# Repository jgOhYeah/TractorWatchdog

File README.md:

# TractorWatchdog
Engine watchdog for a Fordson Dexta tractor. Should work with other tractors as well.

Doxygen documentation is available [here](https://jgohyeah.github.io/TractorWatchdog/).

## Block diagram

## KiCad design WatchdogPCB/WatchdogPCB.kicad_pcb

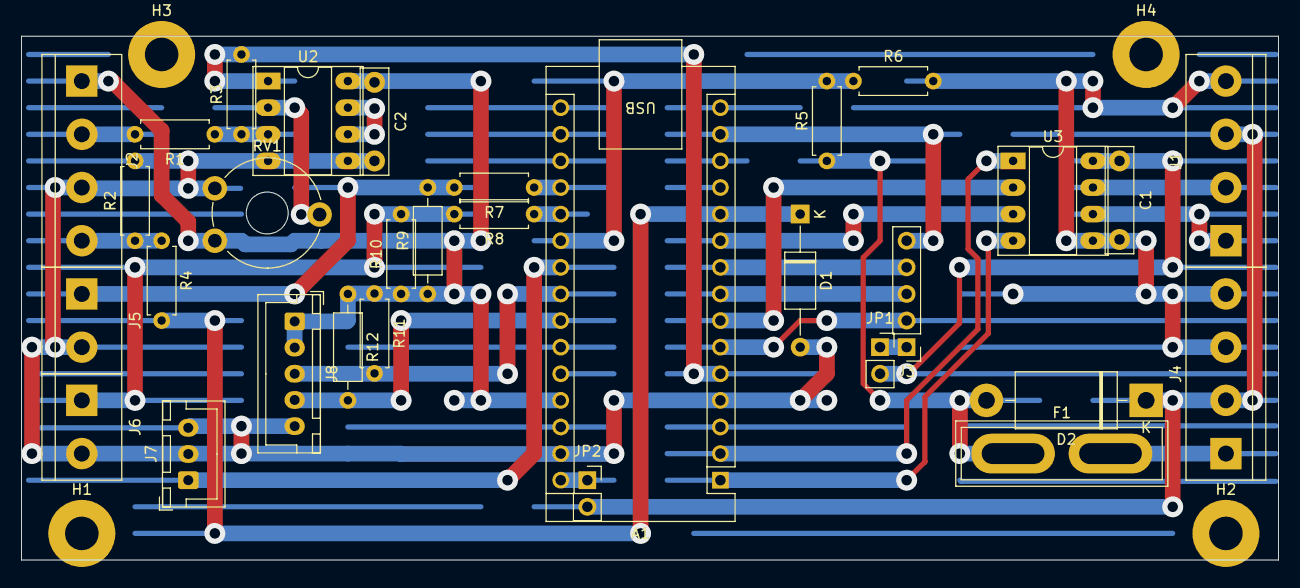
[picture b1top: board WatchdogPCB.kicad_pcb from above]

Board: 4 copper layers, 120.0 x 50.0 mm, 35 parts (0 on the bottom side), 32 nets.

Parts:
A1: Arduino_Nano_v3.x; Arduino_Nano
C1, C2: 10n; C_Rect_L10.0mm_W2.5mm_P7.50mm_MKS4
D1: 5.1V; D_A-405_P12.70mm_Horizontal
D2: 1N5404; D_DO-201AD_P15.24mm_Horizontal
F1: 3A; Fuse_Blade_ATO_directSolder
H1, H2, H3, H4: MountingHole; MountingHole_3.2mm_M3_Pad
J1: Roll hoop; TerminalBlock_bornier-4_P5.08mm
J2: Speed & Oil; TerminalBlock_bornier-4_P5.08mm
J3: H bridge driver control; PinHeader_1x05_P2.54mm_Vertical
J4: Power; TerminalBlock_bornier-4_P5.08mm
J5: Thermistor 1; TerminalBlock_bornier-2_P5.08mm
J6: Thermistor 2; TerminalBlock_bornier-2_P5.08mm
J7: Dashboard A; JST_XH_B3B-XH-A_1x03_P2.50mm_Vertical
J8: Dashboard B; JST_XH_B5B-XH-A_1x05_P2.50mm_Vertical
JP1: 5V jumper; PinSocket_1x02_P2.54mm_Vertical
JP2: 12V jumper; PinSocket_1x02_P2.54mm_Vertical
R1, R4, R11: 4.7k; R_Axial_DIN0207_L6.3mm_D2.5mm_P7.62mm_Horizontal
R2, R7, R8: 1k; R_Axial_DIN0207_L6.3mm_D2.5mm_P7.62mm_Horizontal
R3: 120k; R_Axial_DIN0207_L6.3mm_D2.5mm_P7.62mm_Horizontal
R5: 100k; R_Axial_DIN0207_L6.3mm_D2.5mm_P7.62mm_Horizontal
R6: 39k; R_Axial_DIN0207_L6.3mm_D2.5mm_P7.62mm_Horizontal
R9: 470; R_Axial_DIN0207_L6.3mm_D2.5mm_P10.16mm_Horizontal
R10: 470; R_Axial_DIN0207_L6.3mm_D2.5mm_P7.62mm_Horizontal
R12: 4.7k; R_Axial_DIN0207_L6.3mm_D2.5mm_P10.16mm_Horizontal
RV1: 10k; Potentiometer_Piher_PT-10-V10_Vertical_Hole
U2: MCP602; DIP-8_W7.62mm_Socket_LongPads
U3: DS3695N; DIP-8_W7.62mm_Socket_LongPads

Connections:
+5V: A1.27 (+5V), C1.1, C2.1, J2.1, J8.1, J8.2, JP1.2 (B), R9.1, R10.1, R11.1, R12.1, RV1.1, U2.8 (V+), U3.8 (VCC)
+12V: D2.1 (K), J1.3, J4.2, JP2.2 (B)
+BATT: D2.2 (A), F1.1, R5.1
+VDC: F1.2, J4.1
/Main PCB/+RS485: J1.1, U3.6 (DO/RI)
/Main PCB/-RS485: J1.2, U3.7 (~DO/RI)
/Main PCB/Aux: A1.14 (D11), J3.5
/Main PCB/Dash. BTN: A1.22 (A3), J7.1
/Main PCB/Dash. SCL: A1.24 (A5), J8.4, R12.2
/Main PCB/Dash. SDA: A1.23 (A4), J8.3, R11.2
/Main PCB/Horn: A1.9 (D6), J3.4
/Main PCB/Motor A: A1.6 (D3), J3.2
/Main PCB/Motor B: A1.8 (D5), J3.3
/Main PCB/Motor driver 5V: J3.1, JP1.1 (A)
/Main PCB/Oil SW: J2.4, R2.1, R4.1
/Main PCB/Tach. hall: J2.2, R1.2
/Main PCB/Thermistor 1: J5.1, R7.2, R9.2
/Main PCB/Thermistor 2: J6.1, R8.2, R10.2
/Main PCB/Threshold adjust: RV1.2, U2.2 (-)
GND: A1.4 (GND), A1.29 (GND), C1.2, C2.2, D1.2 (A), J1.4, J2.3, J4.3, J4.4, J5.2, J6.2, J7.2, J7.3, J8.5, R2.2, R6.2, RV1.3, U2.4 (V-), U2.5 (+), U3.5 (GND)
unnamed: A1.19 (A0), R7.1
unnamed: A1.20 (A1), R8.1
unnamed: A1.21 (A2), R5.2, R6.1
unnamed: A1.2 (D0/RX), U3.1 (RO)
unnamed: A1.1 (D1/TX), U3.4 (DI)
unnamed: A1.5 (D2), R3.2, U2.1
unnamed: A1.7 (D4), U3.2 (~RE)
unnamed: A1.10 (D7), U3.3 (DE)
unnamed: A1.11 (D8), D1.1 (K), R4.2
unnamed: A1.30 (VIN), JP2.1 (A)
unnamed: R1.1, R3.1, U2.3 (+)
unnamed: U2.6 (-), U2.7

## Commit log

2023-10-03 Started Arduno code
2023-10-03 Started PCB schematic
2023-10-03 About display works, display structure ongoing
2023-10-03 Home and error displays started, display managing works
2023-10-03 Home and error displays show data
2023-10-03 Temperature and voltage displays should work.
2023-10-03 drawState automatically called for the active state only
2023-10-03 Added doxygen
2023-10-03 Added readme file to doxygen with block diagram
2023-10-03 Deploying to gh-pages from @ jgOhYeah/TractorWatchdog@66a84c4cfc01eea5ef9e85b0e8ce081e668e4cee 🚀
2023-10-03 Initial gh-pages commit
2023-10-11 Started working on dashboard enclosure
2023-10-11 Deploying to gh-pages from @ jgOhYeah/TractorWatchdog@f4bf1ece06eab8d8c2045e530ada4d6bf3068222 🚀
2023-10-11 Chunky dashboard enclosure design completed
2023-10-12 Mechanical side of main unit designed
2023-10-12 Working on electronics enclosure
2023-10-13 Working on the schematic
2023-10-13 Schematic finished
2023-10-13 Layout mostly done
2023-10-14 Made fold go in two parts
2023-10-14 Board layout as contructed
2023-10-15 Added button to UI
2023-10-15 Deploying to gh-pages from @ jgOhYeah/TractorWatchdog@bb199354caf6e690c3105aca5bad56b1517cbab6 🚀
2023-10-15 Autoformatting
2023-10-15 Most sensors added
2023-10-15 Deploying to gh-pages from @ jgOhYeah/TractorWatchdog@bedf9a79883e9635bca10e1fcfefe7930e42f3a0 🚀
2023-10-15 Added state checking, motor control, init screens and bug fixes
2023-10-15 Deploying to gh-pages from @ jgOhYeah/TractorWatchdog@d0365db719fc78dc5e4a14963c554e48b9c63fa7 🚀
2023-10-16 Added timekeeping capabilities hopefully
2023-10-16 Deploying to gh-pages from @ jgOhYeah/TractorWatchdog@f8c32a56cf8dc41646a823f7055e96f66b06238e 🚀
2023-10-17 Demonstration ready
2023-10-17 Deploying to gh-pages from @ jgOhYeah/TractorWatchdog@8c00ade64e00c7b973194b41744bc4b3d9e471bb 🚀
2023-11-02 Tidying up, added credits display back again
2023-11-02 Deploying to gh-pages from @ jgOhYeah/TractorWatchdog@1e9ab7f19c259e3816124b9f23ba17b9ee206fe2 🚀
2023-12-27 Adding pinout to PCB and tidying up CAD
2023-12-28 Schematics modified to use pages for wiring diagram, remote unit started, working on enclosure.
